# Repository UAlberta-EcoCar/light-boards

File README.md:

# light-boards
boards for the head and tail lights and required hardware

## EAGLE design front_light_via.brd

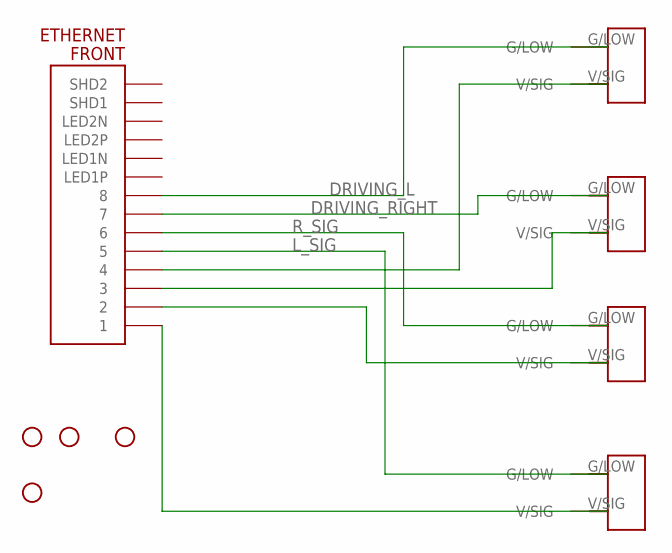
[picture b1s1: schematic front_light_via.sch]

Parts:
FRONT: ETHERNET; A122645-ND
H1, H2, H3, H4: STAND-OFF
U$1, U$2, U$3, U$4: 2_PIN_TECONNECTOR; 2_PIN_CONNECT

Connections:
DRIVING_L: FRONT.P$8 (8), U$1.G/LOW
DRIVING_RIGHT: FRONT.P$7 (7), U$2.G/LOW
L_SIG: FRONT.P$5 (5), U$4.G/LOW
unnamed: FRONT.P$4 (4), U$1.V/SIG
unnamed: FRONT.P$3 (3), U$2.V/SIG
unnamed: FRONT.P$2 (2), U$3.V/SIG
unnamed: FRONT.P$1 (1), U$4.V/SIG
R_SIG: FRONT.P$6 (6), U$3.G/LOW

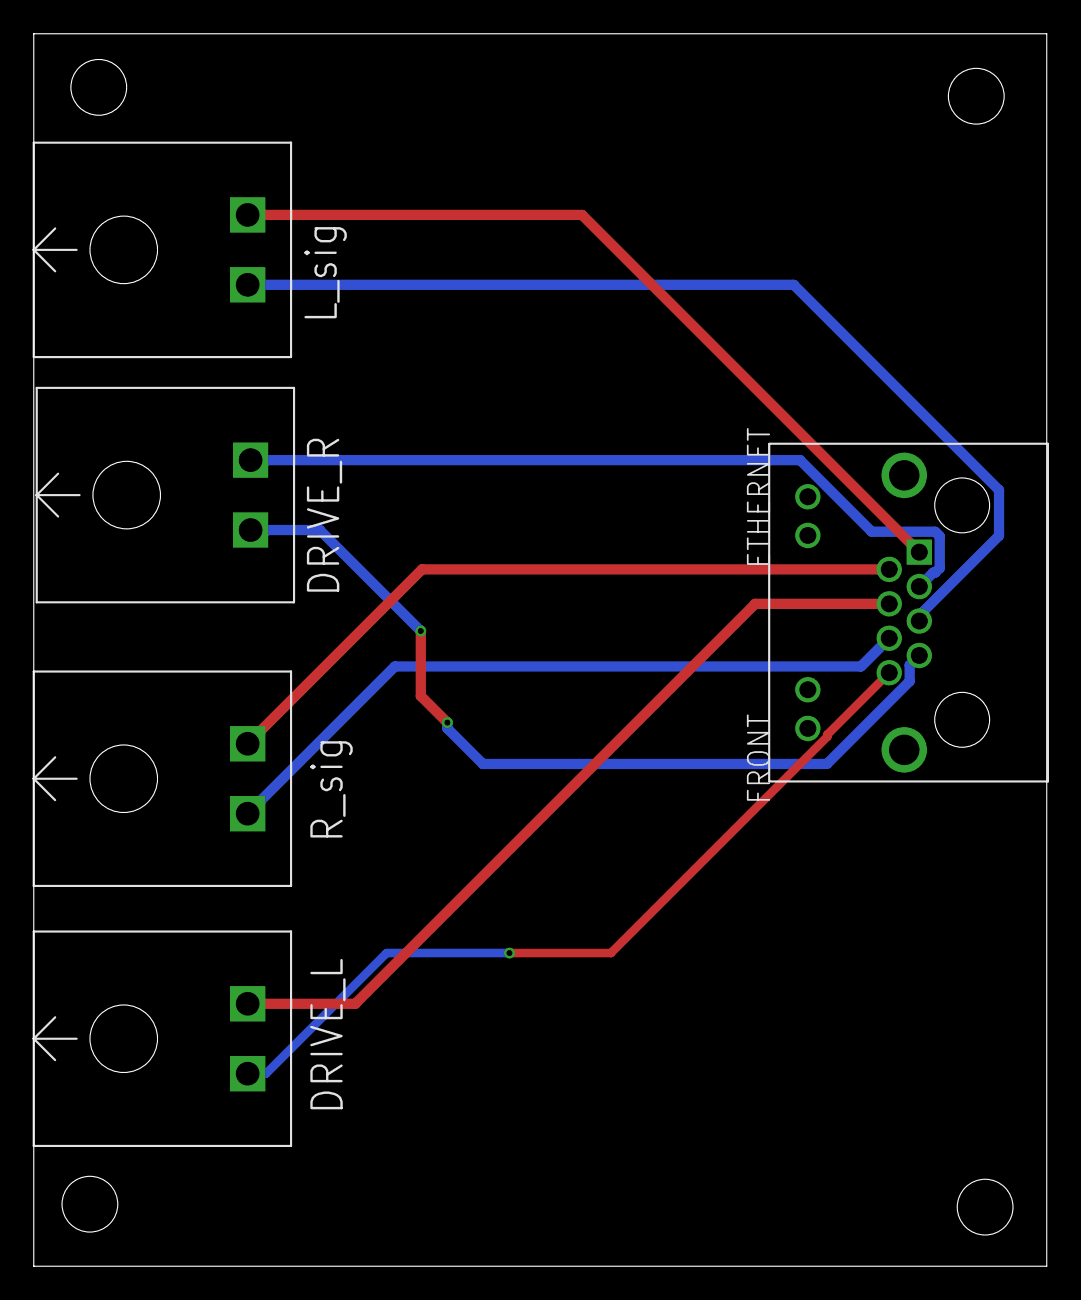
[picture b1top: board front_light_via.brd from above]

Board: 2 copper layers, 60.0 x 73.0 mm, 9 parts (0 on the bottom side), 8 nets.

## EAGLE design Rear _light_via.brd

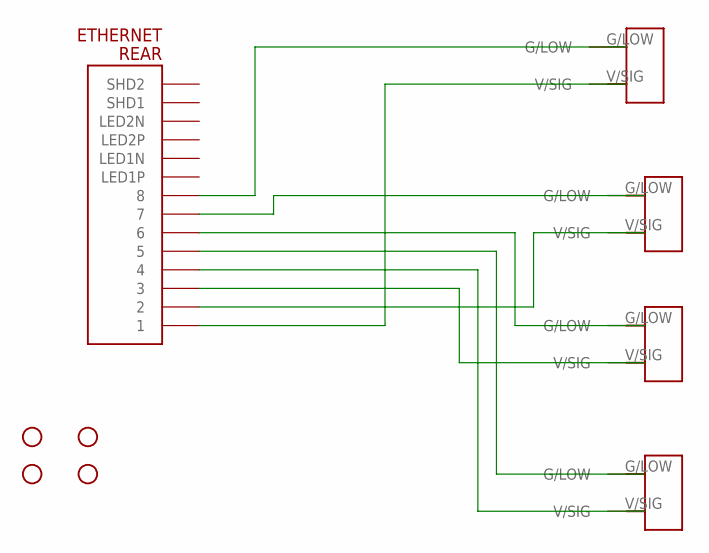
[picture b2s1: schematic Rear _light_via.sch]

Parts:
H1, H2, H3, H4: STAND-OFF
REAR: ETHERNET; A122645-ND
U$1, U$2, U$3, U$4: 2_PIN_TECONNECTOR; 2_PIN_CONNECT

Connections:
unnamed: REAR.P$8 (8), U$1.G/LOW
unnamed: REAR.P$7 (7), U$2.G/LOW
unnamed: REAR.P$6 (6), U$3.G/LOW
unnamed: REAR.P$5 (5), U$4.G/LOW
unnamed: REAR.P$4 (4), U$4.V/SIG
unnamed: REAR.P$3 (3), U$3.V/SIG
unnamed: REAR.P$2 (2), U$2.V/SIG
unnamed: REAR.P$1 (1), U$1.V/SIG

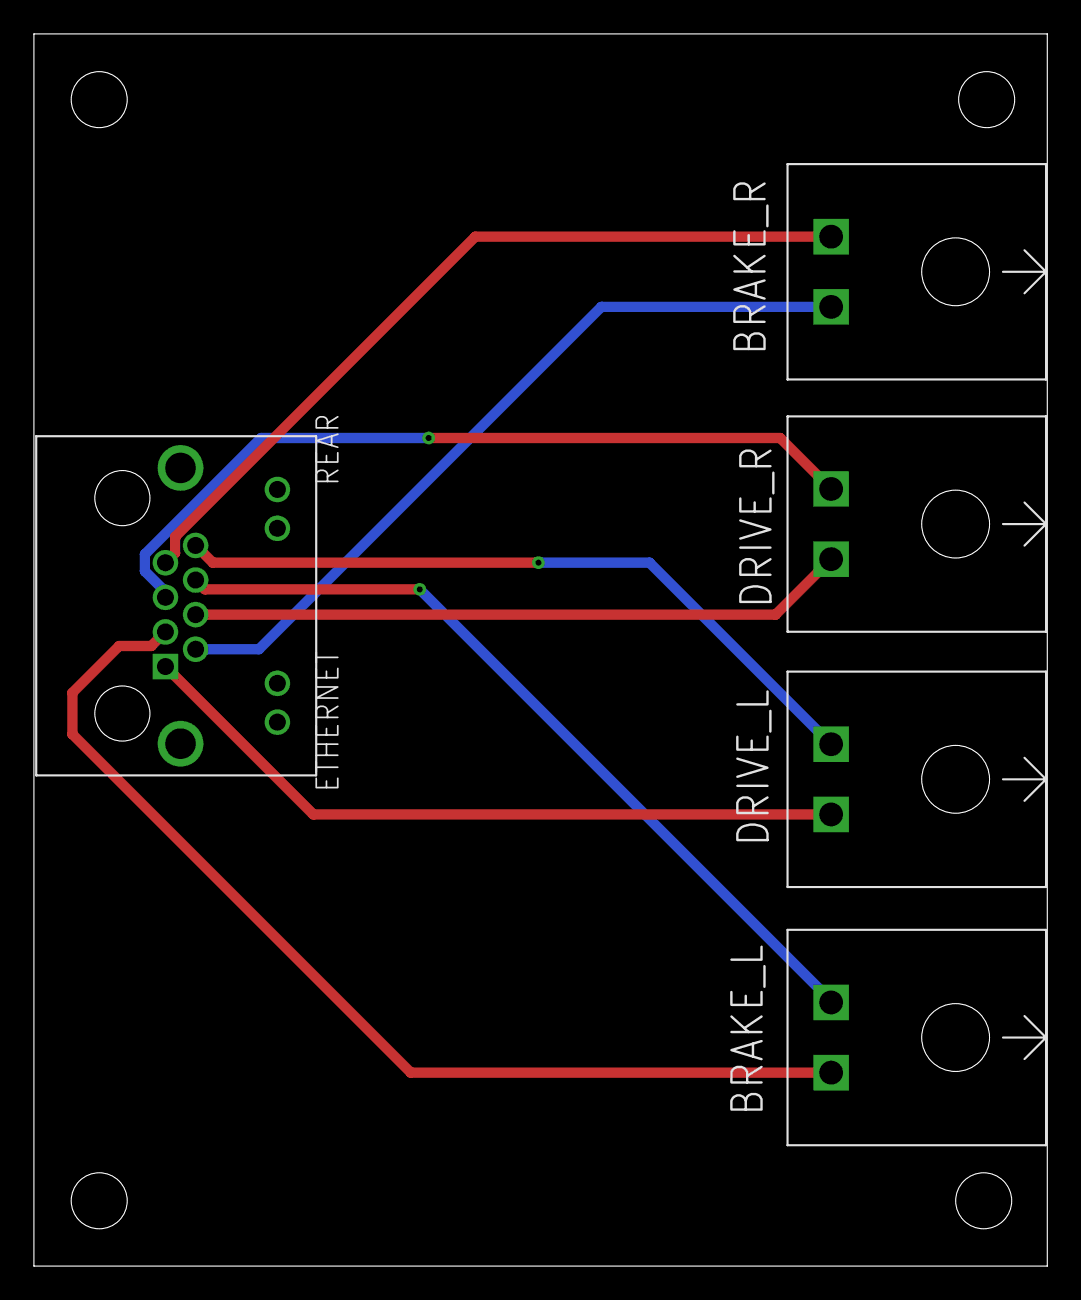
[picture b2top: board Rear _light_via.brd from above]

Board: 2 copper layers, 59.8 x 72.7 mm, 9 parts (0 on the bottom side), 8 nets.

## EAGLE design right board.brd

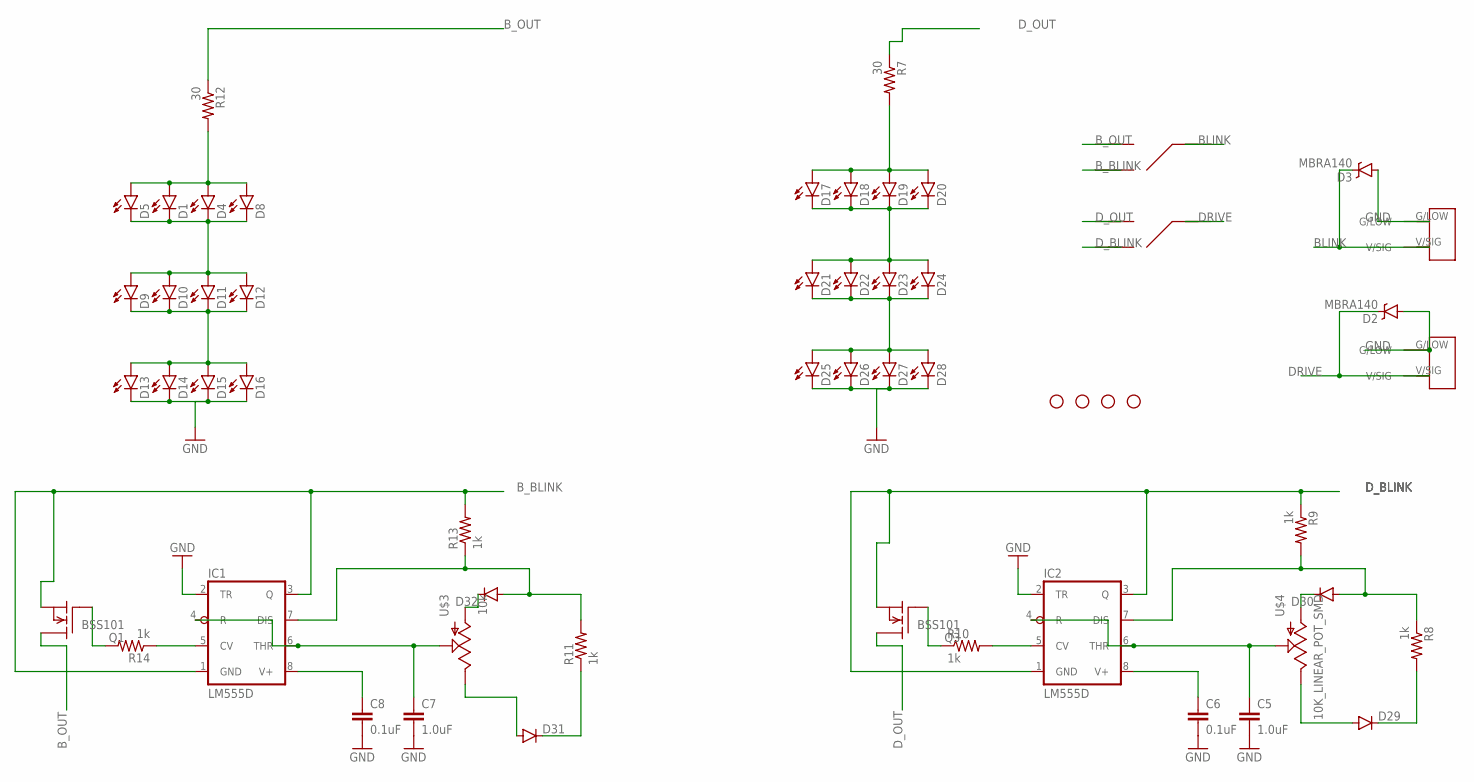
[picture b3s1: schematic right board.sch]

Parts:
C5, C7: 1.0uF; 0805-CAP
C6, C8: 0.1uF; 0603-CAP
D1, D4, D5, D8, D9, D10, D11, D12, D13, D14, D15, D16, D17, D18, D19, D20, D21, D22, D23, D24, D25, D26, D27, D28: LED5MM
D2, D3: MBRA140; SMA-DIODE
D29, D30, D31, D32: DIODESMA; SMA-DIODE
H1, H2, H3, H4: STAND-OFF
IC1, IC2: LM555D; SO08
Q1, Q3: BSS101; TO92
R7, R12: 30; 0805
R8, R9, R10, R11, R13, R14: 1k; 0805
U$1, U$2: JS_SERIES_SLIDESWITCCH; MYPART3
U$3: 10k; TC33X
U$4: 10K_LINEAR_POT_SMD; TC33X
U$5, U$6: 2_PIN_TECONNECTOR; 2_PIN_CONNECT

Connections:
BLINK: D3.C, U$1.IN, U$5.V/SIG
B_BLINK: IC1.1 (GND), IC1.3 (Q), Q1.1 (S), R13.2, U$1.OUT1
B_OUT: Q1.3 (D), R12.1, U$1.OUT2
DRIVE: D2.C, U$2.IN, U$6.V/SIG
D_BLINK: IC2.1 (GND), IC2.3 (Q), Q3.1 (S), R9.1, U$2.OUT1
D_OUT: Q3.3 (D), R7.1, U$2.OUT2
GND: C5.2, C6.2, C7.2, C8.2, D2.A, D3.A, D13.K (C), D14.K (C), D15.K (C), D16.K (C), D25.K (C), D26.K (C), D27.K (C), D28.K (C), IC1.2 (TR), IC2.2 (TR), U$5.G/LOW, U$6.G/LOW
unnamed: D29.A, U$4.3 (E)
unnamed: C5.1, IC2.4 (R), IC2.6 (THR), U$4.2 (S)
unnamed: D32.C, U$3.1 (A)
unnamed: D32.A, IC1.7 (DIS), R11.2, R13.1
unnamed: D31.A, U$3.3 (E)
unnamed: C8.1, IC1.8 (V+)
unnamed: D31.C, R11.1
unnamed: Q1.2 (G), R14.2
unnamed: D30.C, U$4.1 (A)
unnamed: IC1.5 (CV), R14.1
unnamed: D1.K (C), D4.K (C), D5.K (C), D8.K (C), D9.A, D10.A, D11.A, D12.A
unnamed: C7.1, IC1.4 (R), IC1.6 (THR), U$3.2 (S)
unnamed: D1.A, D4.A, D5.A, D8.A, R12.2
unnamed: D30.A, IC2.7 (DIS), R8.1, R9.2
unnamed: C6.1, IC2.8 (V+)
unnamed: IC2.5 (CV), R10.2
unnamed: D17.K (C), D18.K (C), D19.K (C), D20.K (C), D21.A, D22.A, D23.A, D24.A
unnamed: D29.C, R8.2
unnamed: Q3.2 (G), R10.1
unnamed: D21.K (C), D22.K (C), D23.K (C), D24.K (C), D25.A, D26.A, D27.A, D28.A
unnamed: D9.K (C), D10.K (C), D11.K (C), D12.K (C), D13.A, D14.A, D15.A, D16.A
unnamed: D17.A, D18.A, D19.A, D20.A, R7.2

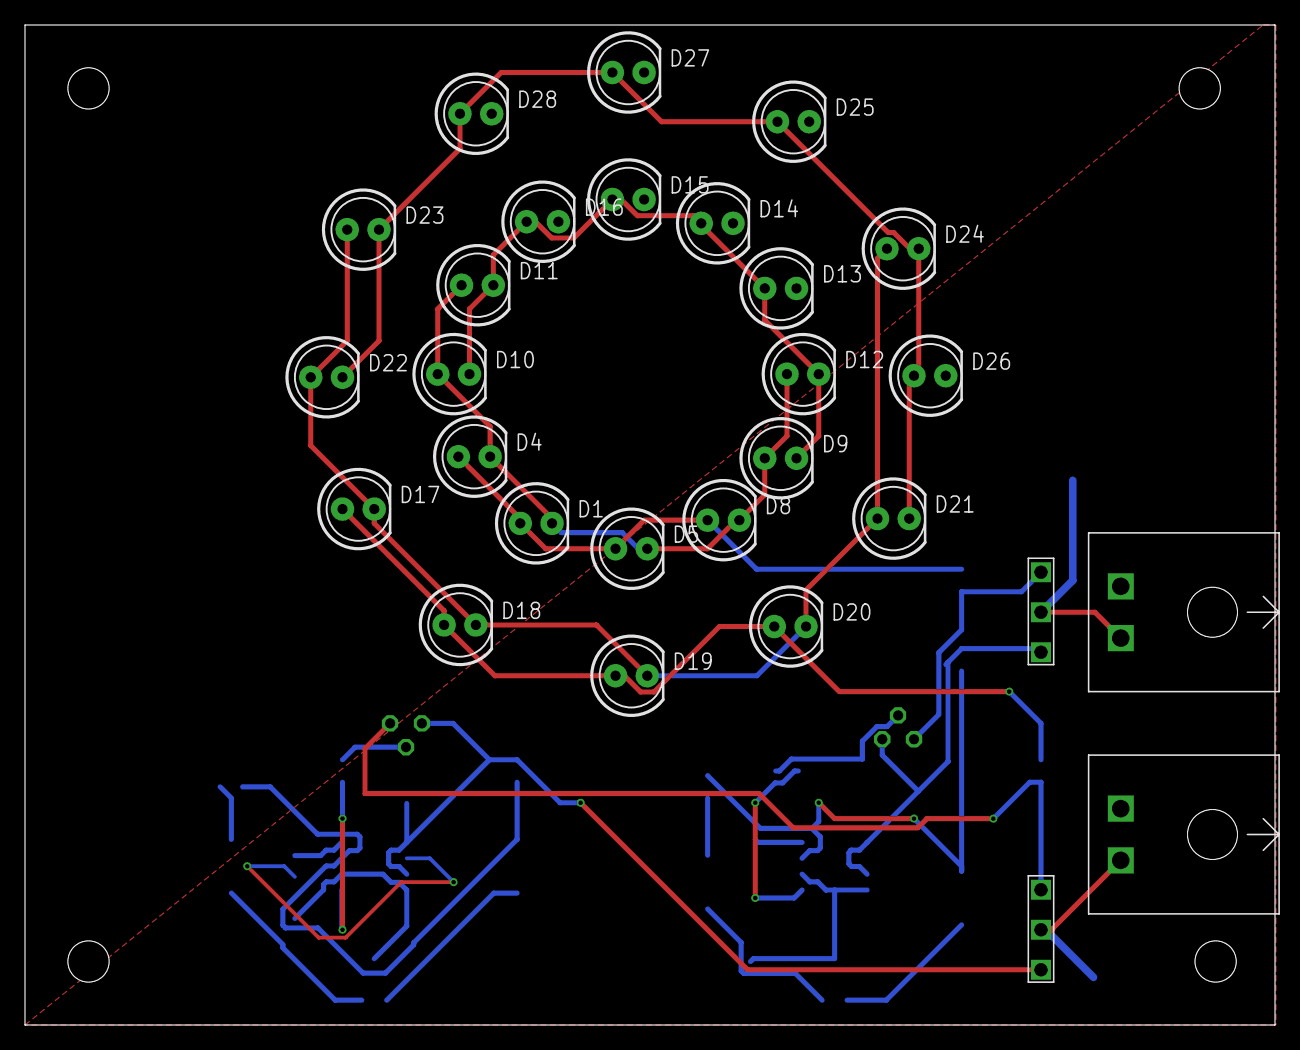
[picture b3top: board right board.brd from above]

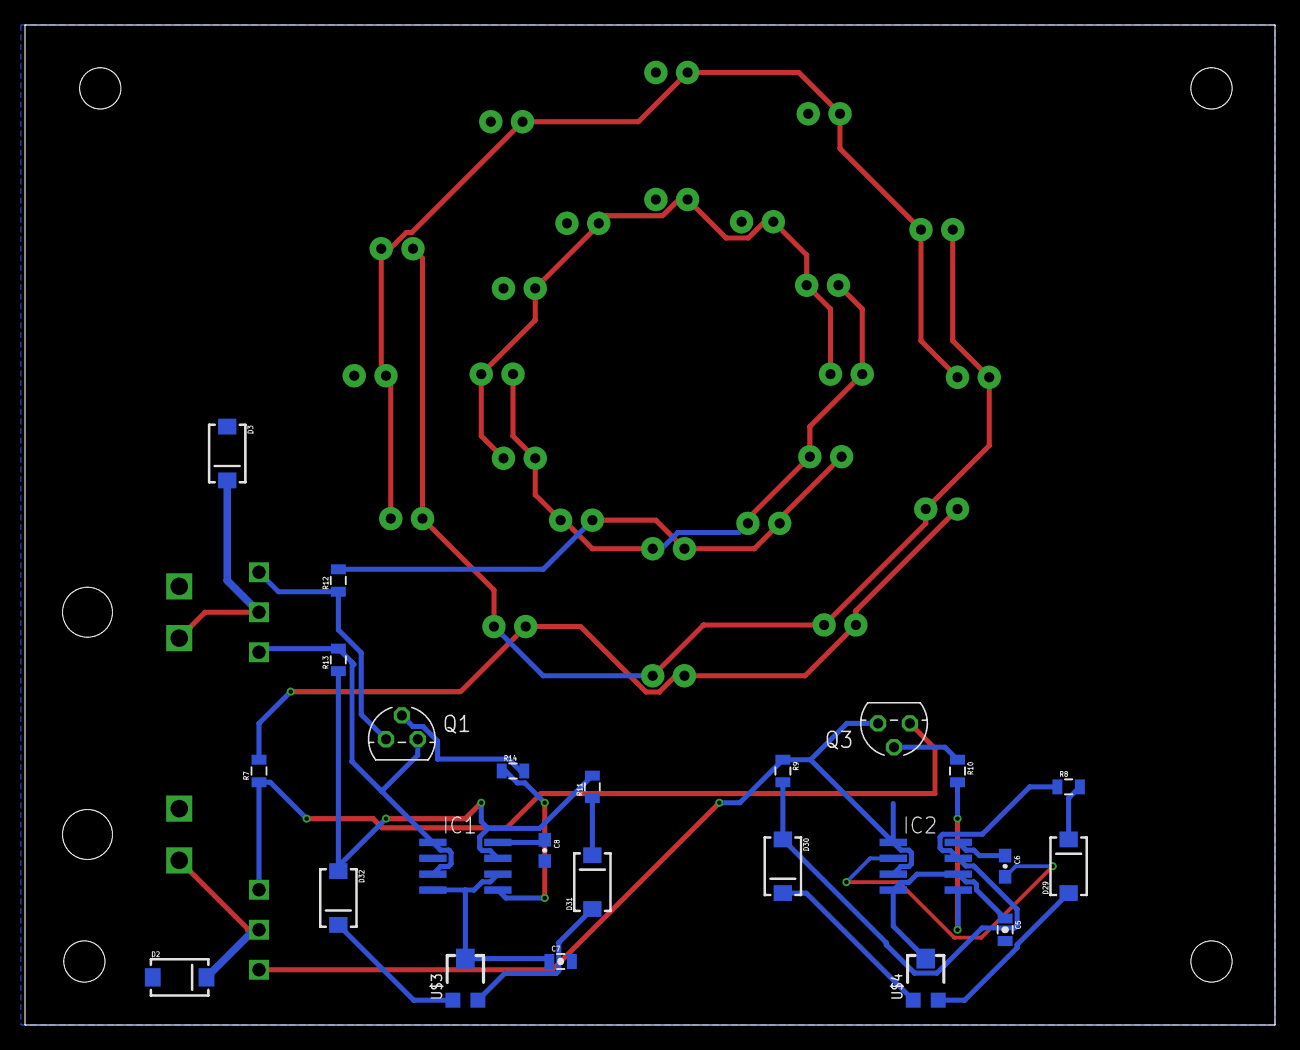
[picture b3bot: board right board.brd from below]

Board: 2 copper layers, 100.0 x 80.0 mm, 56 parts (24 on the bottom side), 29 nets.

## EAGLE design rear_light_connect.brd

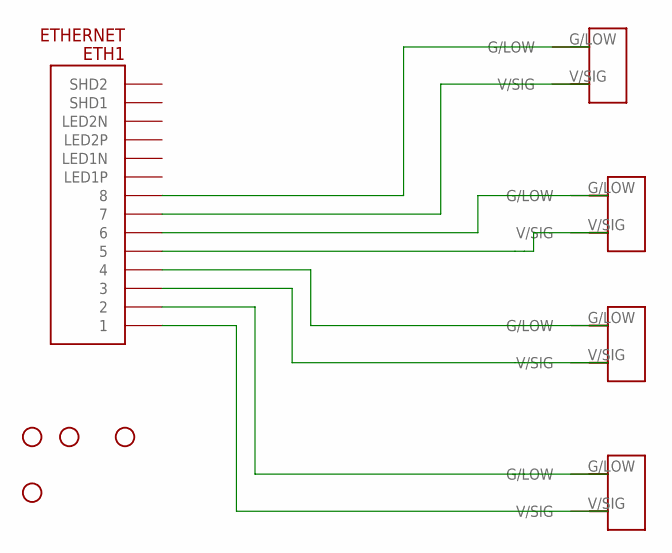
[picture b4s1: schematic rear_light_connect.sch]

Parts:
ETH1: ETHERNET; A122645-ND
H1, H2, H3, H4: STAND-OFF
L_DRIVE: 2_PIN_TECONNECTOR; 2_PIN_CONNECT
L_SIG: 2_PIN_TECONNECTOR; 2_PIN_CONNECT
R-DRIVE: 2_PIN_TECONNECTOR; 2_PIN_CONNECT
R_SIG: 2_PIN_TECONNECTOR; 2_PIN_CONNECT

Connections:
unnamed: ETH1.P$1 (1), R-DRIVE.V/SIG
unnamed: ETH1.P$2 (2), R-DRIVE.G/LOW
unnamed: ETH1.P$3 (3), L_DRIVE.V/SIG
unnamed: ETH1.P$4 (4), L_DRIVE.G/LOW
unnamed: ETH1.P$5 (5), R_SIG.V/SIG
unnamed: ETH1.P$6 (6), R_SIG.G/LOW
unnamed: ETH1.P$7 (7), L_SIG.V/SIG
unnamed: ETH1.P$8 (8), L_SIG.G/LOW

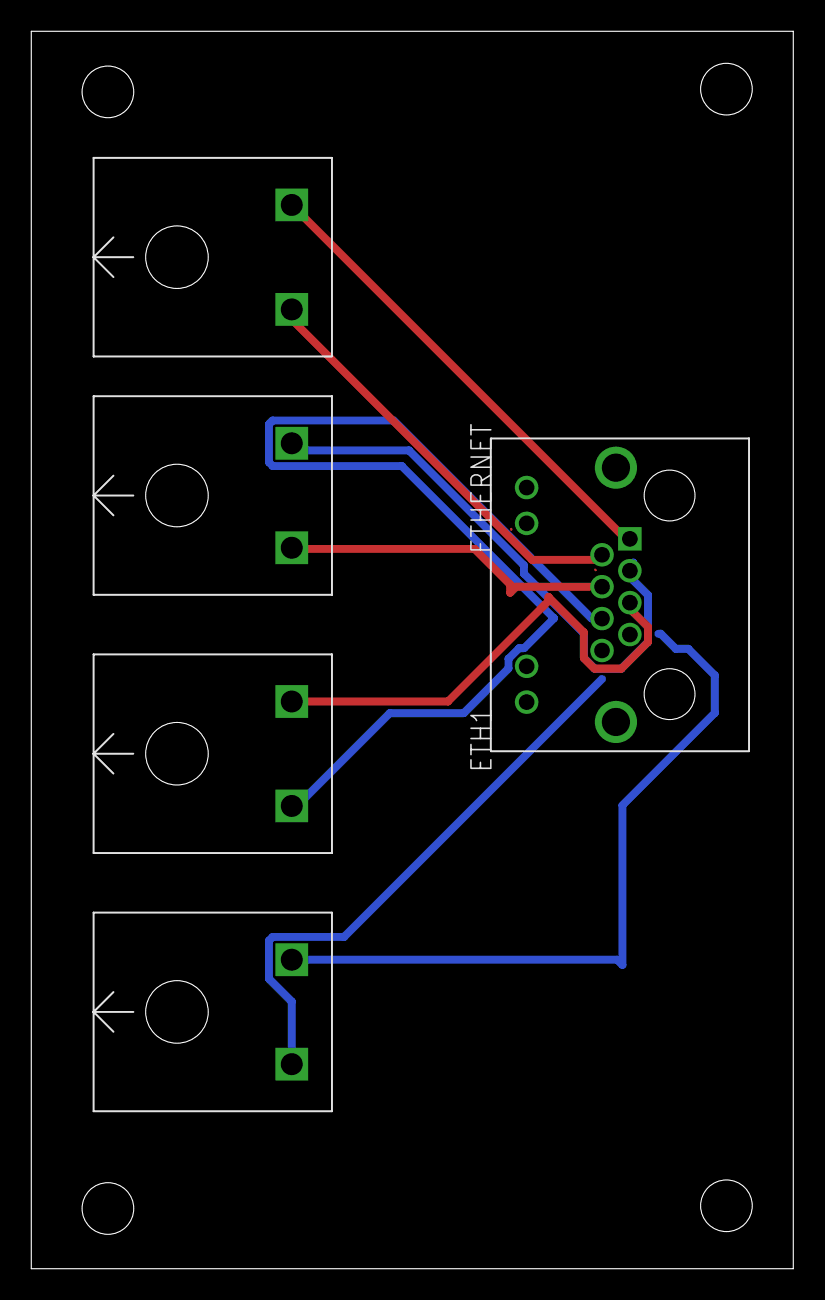
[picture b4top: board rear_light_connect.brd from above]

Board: 2 copper layers, 48.7 x 79.1 mm, 9 parts (0 on the bottom side), 8 nets.

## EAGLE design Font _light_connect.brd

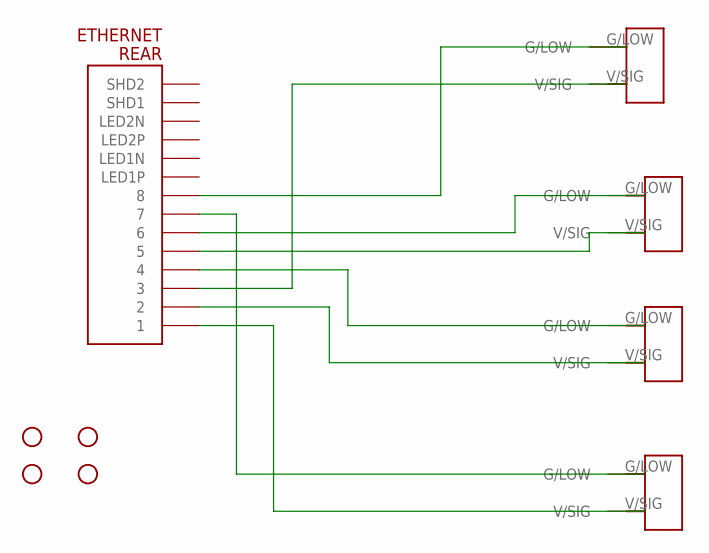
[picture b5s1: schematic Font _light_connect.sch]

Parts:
H1, H2, H3, H4: STAND-OFF
L_DRIVE: 2_PIN_TECONNECTOR; 2_PIN_CONNECT
L_SIG: 2_PIN_TECONNECTOR; 2_PIN_CONNECT
REAR: ETHERNET; A122645-ND
R_SIG: 2_PIN_TECONNECTOR; 2_PIN_CONNECT
T_DRIVE: 2_PIN_TECONNECTOR; 2_PIN_CONNECT

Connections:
unnamed: L_DRIVE.V/SIG, REAR.P$1 (1)
unnamed: L_SIG.V/SIG, REAR.P$2 (2)
unnamed: REAR.P$5 (5), R_SIG.V/SIG
unnamed: L_SIG.G/LOW, REAR.P$4 (4)
unnamed: L_DRIVE.G/LOW, REAR.P$7 (7)
unnamed: REAR.P$6 (6), R_SIG.G/LOW
unnamed: REAR.P$3 (3), T_DRIVE.V/SIG
unnamed: REAR.P$8 (8), T_DRIVE.G/LOW

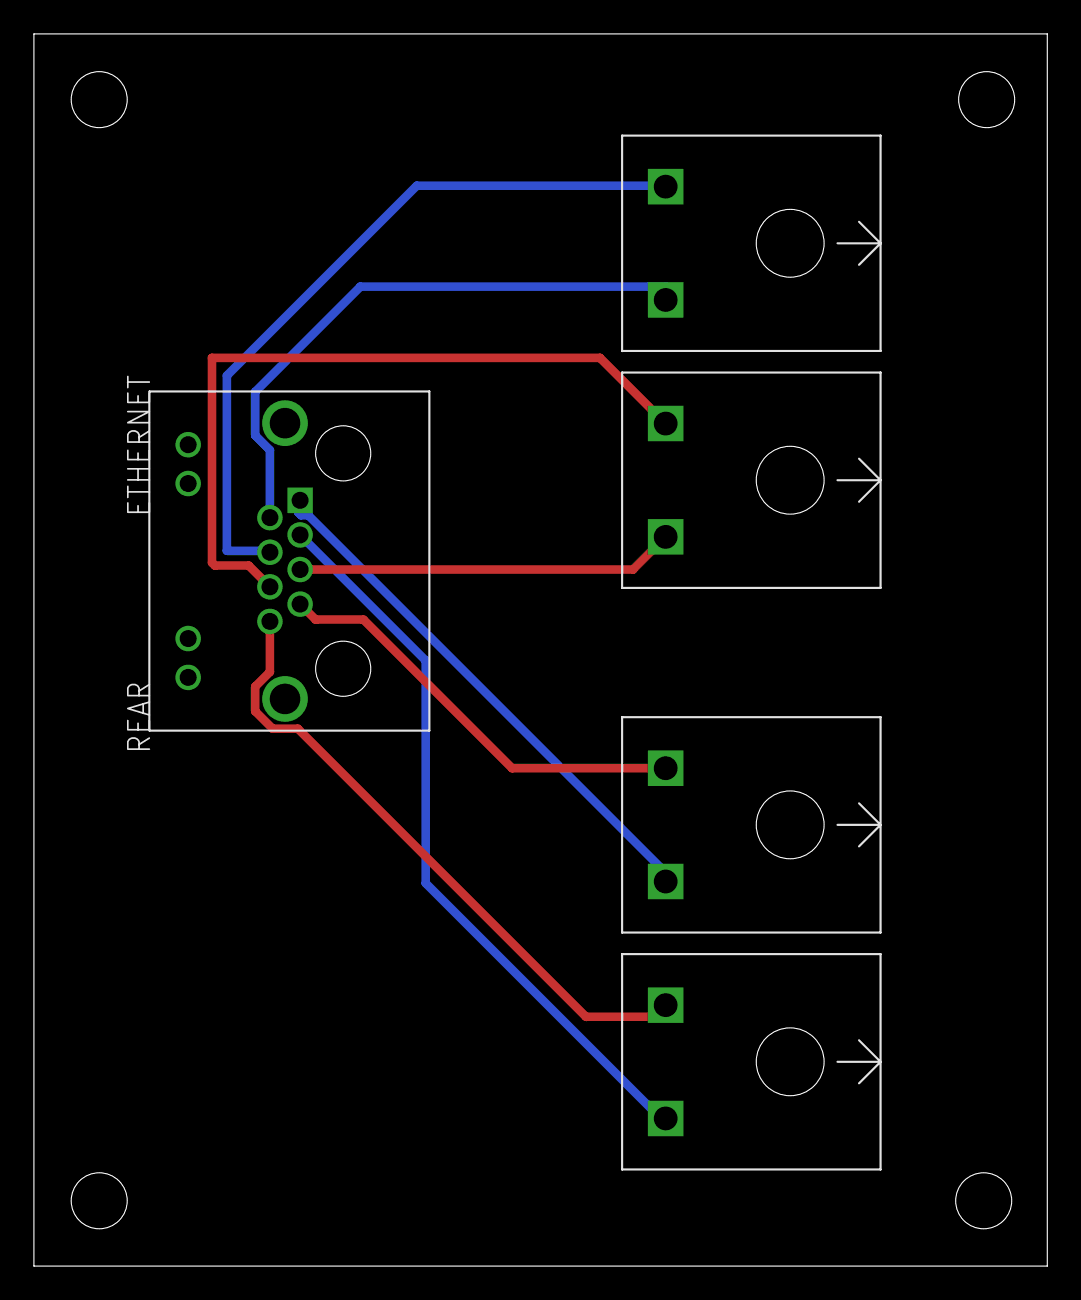
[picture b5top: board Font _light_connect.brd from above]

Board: 2 copper layers, 59.8 x 72.7 mm, 9 parts (0 on the bottom side), 8 nets.

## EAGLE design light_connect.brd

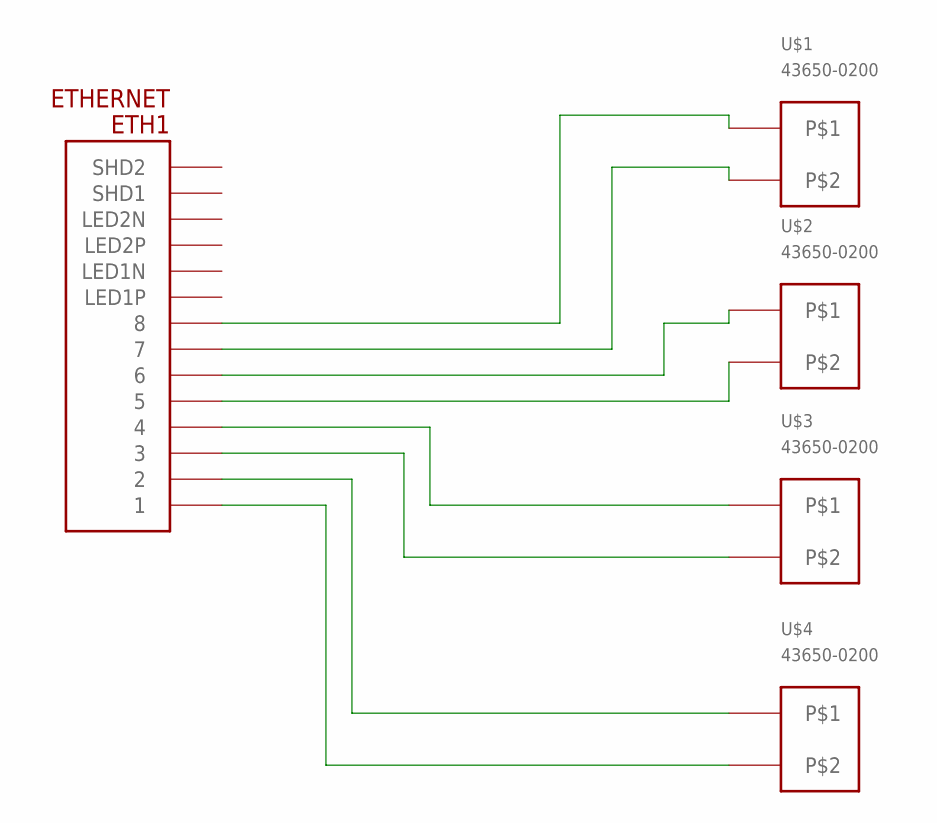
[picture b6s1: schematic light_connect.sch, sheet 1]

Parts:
ETH1: ETHERNET; A122645-ND
U$1, U$2, U$3, U$4: 43650-0200

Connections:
unnamed: ETH1.P$1 (1), U$4.P$1
unnamed: ETH1.P$2 (2), U$4.P$2
unnamed: ETH1.P$3 (3), U$3.P$1
unnamed: ETH1.P$4 (4), U$3.P$2
unnamed: ETH1.P$5 (5), U$2.P$1
unnamed: ETH1.P$6 (6), U$2.P$2
unnamed: ETH1.P$7 (7), U$1.P$1
unnamed: ETH1.P$8 (8), U$1.P$2

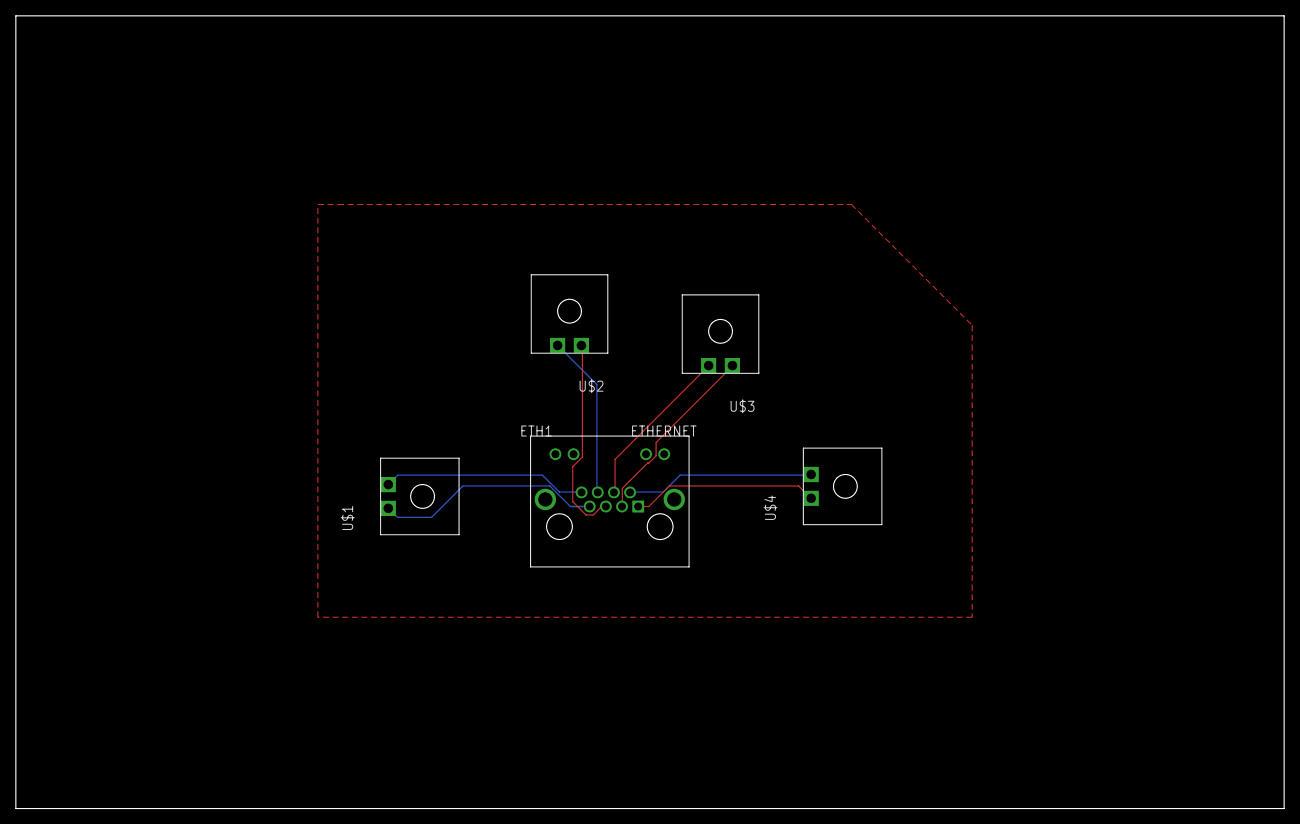
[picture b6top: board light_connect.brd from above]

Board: 2 copper layers, 160.0 x 100.0 mm, 5 parts (0 on the bottom side), 8 nets.

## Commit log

2017-10-28 inital boards
    pwm circuit schematic and the lighting boards
2017-11-20 interconeects V.1
    added new interconnect boards
2017-11-26 updated to match all the pinouts
    left, right, front, back, connections consistent PWM added to the light boards
2017-12-02 routed transfer boards
2017-12-02 added switches to light board
2017-12-02 updated mosfets on lights
2017-12-12 updated for correct fets and routing
2018-01-27 Gerbers generated
2018-01-27 all gerbers generated
2018-02-10 via gerbers generated
    via boards completed and gerbers generated
2018-02-26 added reverse polairity protection
2018-05-06 correct all routing errors

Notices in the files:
parts and their libraries:
SparkFun-Electromechanical: Licensing: Creative Commons ShareAlike 4.0 International - https://creativecommons.org/licenses/by-sa/4.0
